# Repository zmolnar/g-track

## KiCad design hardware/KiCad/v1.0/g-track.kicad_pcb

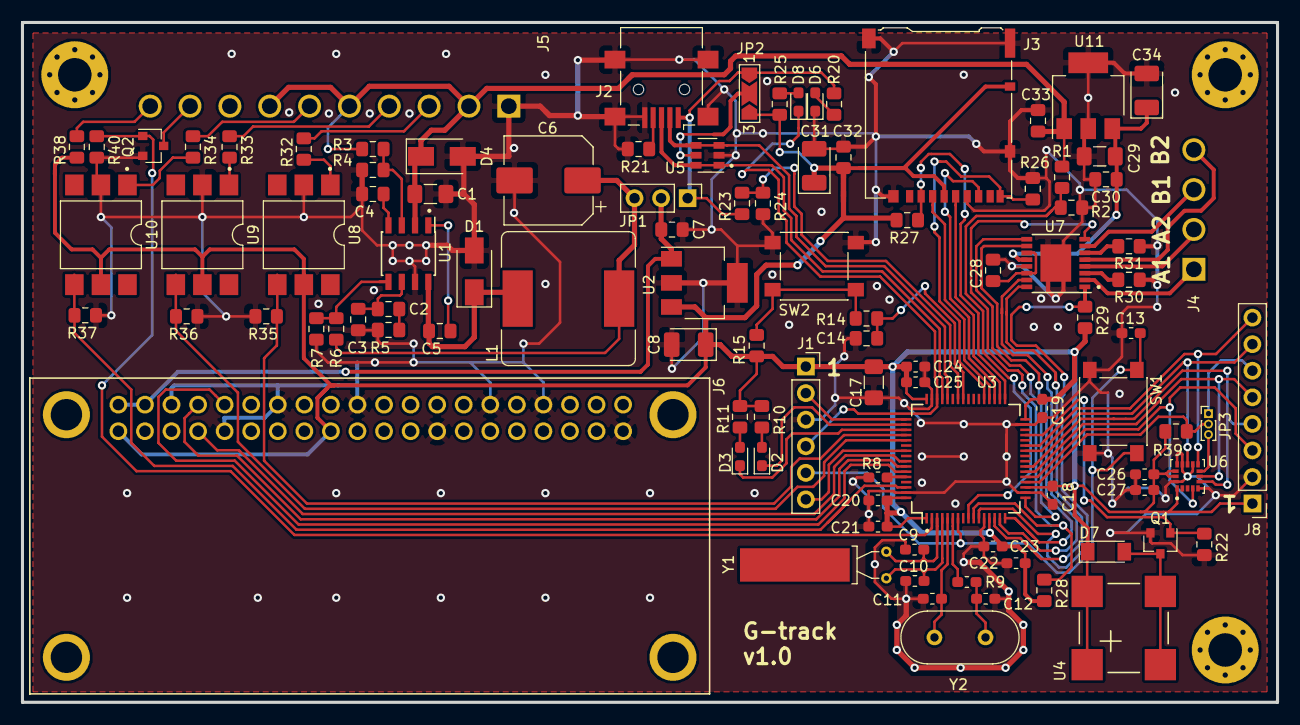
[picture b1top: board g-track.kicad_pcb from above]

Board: 2 copper layers, 120.0 x 65.0 mm, 101 parts (0 on the bottom side), 81 nets.

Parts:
C1, C17, C29: 10uF/25V; C_1206_3216Metric_Pad1.42x1.75mm_HandSolder
C2: 220pF; C_0805_2012Metric_Pad1.15x1.40mm_HandSolder
C3: 56pF; C_0805_2012Metric_Pad1.15x1.40mm_HandSolder
C4: 15nF; C_0805_2012Metric_Pad1.15x1.40mm_HandSolder
C5, C14, C32: 100nF; C_0805_2012Metric_Pad1.15x1.40mm_HandSolder
C6: 470uF; CP_Elec_8x10
C7, C33: 470nF; C_0805_2012Metric_Pad1.15x1.40mm_HandSolder
C8, C31, C34: 47uF; CP_EIA-3528-21_Kemet-B_Pad1.50x2.35mm_HandSolder
C9, C10: 12pF; C_0603_1608Metric_Pad1.05x0.95mm_HandSolder
C11, C12: 22pF; C_0603_1608Metric_Pad1.05x0.95mm_HandSolder
C13, C18, C19, C20, C21, C23, C25, C27: 100nF; C_0603_1608Metric_Pad1.05x0.95mm_HandSolder
C22, C24: 1uF; C_0603_1608Metric_Pad1.05x0.95mm_HandSolder
C26: 10uF; C_0603_1608Metric_Pad1.05x0.95mm_HandSolder
C28: 2.2uF; C_0805_2012Metric_Pad1.15x1.40mm_HandSolder
C30: 100nF/50V; C_0805_2012Metric_Pad1.15x1.40mm_HandSolder
D1, D4: B340A; D_SMA
D2, D3, D6: GREEN; D_0603_1608Metric_Pad1.05x0.95mm_HandSolder
D7: LL46; D_MiniMELF
D8: RED; D_0603_1608Metric_Pad1.05x0.95mm_HandSolder
J1: SWD; PinSocket_1x06_P2.54mm_Vertical
J2: USB_B_Mini; USB_Mini-B_Lumberg_2486_01_Horizontal
J3: Micro SD card; microSD_HC_Hirose_DM3AT-SF-PEJM5
J4: DCM; Tianli_TLPHC100R_1x04_P3.81mm_Horizontal
J5: EXT; Tianli_TLPHC100R_1x10_P3.81mm_Horizontal
J6: Waveshare GSM/GPS/GNSS; Waveshare_GSM_GPS_GNSS_hat
J8: LIS3DSH; PinHeader_1x08_P2.54mm_Vertical
JP1: Power source; PinHeader_1x03_P2.54mm_Vertical
JP2: Protection; SolderJumper-3_P2.0mm_Open_TrianglePad1.0x1.5mm_NumberLabels
JP3: ACC_SPI_SELECT; PinHeader_1x03_P1.00mm_Vertical
L1: 22uH; L_Bourns_SRR1260
Q1, Q2: 2N7002; SOT-23
R1: 75k; R_0805_2012Metric_Pad1.15x1.40mm_HandSolder
R2, R35, R36, R37: 15k; R_0805_2012Metric_Pad1.15x1.40mm_HandSolder
R3: 332k; R_0805_2012Metric_Pad1.15x1.40mm_HandSolder
R4: 68k1; R_0805_2012Metric_Pad1.15x1.40mm_HandSolder
R5: 40k2; R_0805_2012Metric_Pad1.15x1.40mm_HandSolder
R6, R15, R22, R26, R27, R28, R29, R39, R40: 10k; R_0805_2012Metric_Pad1.15x1.40mm_HandSolder
R7: 1k91; R_0805_2012Metric_Pad1.15x1.40mm_HandSolder
R8: 10k; R_0603_1608Metric_Pad1.05x0.95mm_HandSolder
R9: 390R; R_0603_1608Metric_Pad1.05x0.95mm_HandSolder
R10, R11, R25, R38: 330R; R_0805_2012Metric_Pad1.15x1.40mm_HandSolder
R14: 160R; R_0805_2012Metric_Pad1.15x1.40mm_HandSolder
R20: 510R; R_0805_2012Metric_Pad1.15x1.40mm_HandSolder
R21: 100k; R_0805_2012Metric_Pad1.15x1.40mm_HandSolder
R23: 33k; R_0805_2012Metric_Pad1.15x1.40mm_HandSolder
R24: 68k; R_0805_2012Metric_Pad1.15x1.40mm_HandSolder
R30, R31: 0R47; R_0805_2012Metric_Pad1.15x1.40mm_HandSolder
R32, R33, R34: 2k; R_0805_2012Metric_Pad1.15x1.40mm_HandSolder
SW1: Reset; SW_SPST_PTS645
SW2: BT0; SW_SPST_PTS645
U1: TPS54233; SOIC-8_3.9x4.9mm_P1.27mm
U2: LM3940IMP*; SOT-223-3_TabPin2
U3: STM32L452RCTx; LQFP-64_10x10mm_P0.5mm
U4: KSSGJ4B20
U5: USBLC6-2SC6; SOT-23-6
U6: LIS3DSH; LGA-16_3x3mm_P0.5mm_LayoutBorder3x5y
U7: DRV8848; TSSOP-16-1EP_4.4x5mm_P0.65mm
U8, U9, U10: CNY17-3; SMDIP-6_W9.53mm
U11: LM2940IMP*; SOT-223-3_TabPin2
Y1: 32.768kHz; Crystal_AT310_D3.0mm_L10.0mm_Horizontal_1EP_style1
Y2: 8MHz; Crystal_HC49-U_Vertical

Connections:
+3V3: C8.1, C17.1, C18.1, C19.1, C20.1, C21.1, C22.1, C23.1, C24.1, C25.1, C26.1, C27.1, C31.1, C32.1, D7.1, J1.1, J3.4, J3.10, J6.1, J6.17, J8.1, JP2.3, R10.1, R11.1, R15.1, R25.1, R27.1, R28.1, R29.1, R38.1, R39.1, U2.3, U3.1, U3.13, U3.19, U3.32, U3.48, U3.64, U4.1, U4.2, U6.1, U6.14, U6.15, U8.5, U9.5, U10.5
+5V: C7.2, J6.2, J6.4, JP1.2, U2.1
+5V_USB: J2.1, JP1.1, JP2.1, R20.1, R23.1
+12V: C29.1, C30.1, C34.1, U7.12, U11.3
+BATT: C1.1, C33.1, D4.1, J5.2, J5.5, J5.7, R1.1, R3.1, U1.2, U11.1
-BATT: C1.2, C3.2, C4.2, C6.2, C7.1, C8.2, C9.1, C10.1, C11.2, C12.2, C13.2, C14.2, C17.2, C18.2, C19.2, C20.2, C21.2, C22.2, C23.2, C24.2, C25.2, C26.2, C27.2, C28.1, C29.2, C30.2, C31.2, C32.2, C33.2, C34.2, D1.2, D4.2, D6.1, J1.3, J2.5, J2.6, J3.6, J3.11, J5.1, J6.6, J6.9, J6.14, J6.20, J6.25, J6.30, J6.34, J6.39, J8.2, Q1.2, Q2.2, R2.2, R4.2, R5.2, R7.2, R8.2, R21.2, R22.2, R24.2, R26.2, R30.1, R31.1, R35.2, R36.2, R37.2, R40.2, SW1.1, SW2.2, U1.7, U2.2, U3.12, U3.18, U3.31, U3.47, U3.63, U5.2, U6.5, U6.10, U6.12, U6.13, U6.16, U7.13, U7.17, U8.2, U9.2, U10.2, U11.2
/DC motor driver/DCM_AIN1: U3.14, U7.16
/DC motor driver/DCM_AIN2: U3.15, U7.15
/DC motor driver/DCM_BIN1: U3.17, U7.9
/DC motor driver/DCM_BIN2: U3.16, U7.10
/DC motor driver/DCM_FAULT: R28.2, U3.10, U7.8
/DC motor driver/DCM_SLEEP: R29.2, U3.11, U7.1
/External/EXT_IGNITION: R35.1, U3.52, U8.4
/External/EXT_LED: Q2.1, R40.1, U3.2
/External/EXT_SW1: R37.1, U3.62, U10.4
/External/EXT_SW2: R36.1, U3.53, U9.4
/External/IGNITION: J5.3, R32.1
/External/LED_ANODE: J5.10, R38.2
/External/LED_CATHODE: J5.9, Q2.3
/External/SW-1: J5.6, R34.1
/External/SW-2: J5.4, R33.1
/Peripherals/ACC_CS: JP3.2, R39.2, U3.20
/Peripherals/ACC_INT1: J8.7, U3.26, U6.11
/Peripherals/ACC_INT2: J8.8, U3.27, U6.9
/Peripherals/ACC_MISO: J8.5, U3.22, U6.7
/Peripherals/ACC_MOSI: J8.4, U3.23, U6.6
/Peripherals/ACC_SCK: J8.3, U3.21, U6.4
/Peripherals/BUZZER_PWM: Q1.1, R22.1, U3.29
/Peripherals/RPI_UART_RX: J6.10, U3.59
/Peripherals/RPI_UART_TX: J6.8, U3.58
/Peripherals/SDC_CARD_DETECT: J3.9, R26.1, U3.37
/Peripherals/SDC_CS: J3.2, R27.2, U3.33
/Peripherals/SDC_MISO: J3.7, U3.35
/Peripherals/SDC_MOSI: J3.3, U3.36
/Peripherals/SDC_SCK: J3.5, U3.34
/Peripherals/USB_D+: J2.3, U3.45, U5.1, U5.6
/Peripherals/USB_D-: J2.2, U3.44, U5.3, U5.4
/Peripherals/USB_LED: D8.1, J1.4, U3.46
/Peripherals/USB_VBUS_SENSE: R23.2, R24.1, U3.42
/Peripherals/WAVESHARE_POWER: J6.7, U3.57
/Sheet5C1D43B5/ADC_VBAT: R1.2, R2.1, U3.9
/mcu/BOOT0: R8.1, U3.60
/mcu/NRST: C13.1, J1.5, SW1.2, U3.7
/mcu/PA8: C14.1, R14.2, U3.41
/mcu/PA14: J1.2, U3.49
/mcu/PA15: D2.1, U3.50
/mcu/PB3: J1.6, U3.55
/mcu/PC10: D3.1, U3.51
/mcu/PC14: C9.2, U3.3, Y1.1
/mcu/PC15: C10.2, U3.4, Y1.2
unnamed: C2.1, C3.1, U1.6
unnamed: C2.2, R5.1
unnamed: C4.1, U1.4
unnamed: C5.1, U1.1
unnamed: C5.2, D1.1, L1.1, U1.8
unnamed: C6.1, JP1.3, L1.2, R6.1
unnamed: C11.1, U3.5, Y2.1
unnamed: C12.1, R9.2, Y2.2
unnamed: C28.2, U7.11, U7.14
unnamed: D2.2, R10.2
unnamed: D3.2, R11.2
unnamed: D6.2, R20.2
unnamed: D7.2, Q1.3, U4.3, U4.4
unnamed: D8.2, R25.2
unnamed: J2.4, R21.1
unnamed: J4.1, U7.2
unnamed: J4.2, U7.4
unnamed: J4.3, U7.7
unnamed: J4.4, U7.5
unnamed: J8.6, JP3.1
unnamed: JP2.2, U5.5
unnamed: JP3.3, U6.8
unnamed: R3.2, R4.1, U1.3
unnamed: R6.2, R7.1, U1.5
unnamed: R9.1, U3.6
unnamed: R14.1, R15.2, SW2.1
unnamed: R30.2, U7.3
unnamed: R31.2, U7.6
unnamed: R32.2, U8.1
unnamed: R33.2, U9.1
unnamed: R34.2, U10.1

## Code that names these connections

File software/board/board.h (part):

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/*
 * GPIOA setup:
 *
 * PA0  - DCM_AIN1                  (output push-pull).
 * PA1  - DCM_AIN2                  (output push-pull).
 * PA2  - DCM_BIN2                  (input pullup).
 * PA3  - DCM_BIN1                  (input pullup).
 * PA4  - ACC_CS                    (input pullup).
 * PA5  - ACC_SCK                   (input pullup).
 * PA6  - ACC_MISO                  (input pullup).
 * PA7  - ACC_MOSI                  (input pullup).
 * PA8  - BT0                       (input pullup).
 * PA9  - USB_VBUS_SENSE            (input pulldown).
 * PA10 - PA10_NC                   (input pullup).
 * PA11 - USB_DM                    (input pullup).
 * PA12 - USB_DP                    (input pullup).
 * PA13 - SWDIO_USB_LED             (alternate 0).
 * PA14 - SWCLK                     (alternate 0).
 * PA15 - LED_2_RED                 (output push-pull).
 */
#define VAL_GPIOA_MODER             (PIN_MODE_OUTPUT(GPIOA_DCM_AIN1)          | \
                                     PIN_MODE_OUTPUT(GPIOA_DCM_AIN2)          | \
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/*
 * GPIOB setup:
 *
 * PB0  - ACC_INT1                  (input pullup).
 * PB1  - ACC_INT2                  (input pullup).
 * PB2  - PB2_NC                    (input pullup).
 * PB3  - SWD_SWO                   (input pullup).
 * PB4  - PB4_NC                    (input pullup).
 * PB5  - WAVESHARE_POWER           (output push-pull).
 * PB6  - RPI_UART_TX               (input pullup).
 * PB7  - RPI_UART_RX               (input pullup).
 * PB8  - PB8_NC                    (input pullup).
 * PB9  - EXT_SW1                   (input push-pull pull-down).
 * PB10 - BUZZER_PWM                (output push-pull).
 * PB11 - PB11_NC                   (input pullup).
 * PB12 - SDC_SPI2_CS               (alternate 5).
 * PB13 - SDC_SPI2_SCK              (alternate 5).
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 * GPIOC setup:
 *
 * PC0  - PC0_NC                    (input pullup).
 * PC1  - ADC_VBAT                  (input pullup).
 * PC2  - DCM_FAULT                 (input pullup).
 * PC3  - DCM_SLEEP                 (output pullup).
 * PC4  - PC4_NC                    (input pullup).
 * PC5  - PC5_NC                    (input pullup).
 * PC6  - SDC_CARD_DETECT           (input pulldown).
 * PC7  - PC7_NC                    (input pullup).
 * PC8  - PC8_NC                    (input pullup).
 * PC9  - PC9_NC                    (input pullup).
 * PC10 - LED_3_GREEN               (output push-pull).
 * PC11 - EXT_IGNITION              (input push-pull pull-down).
 * PC12 - EXT_SW2                   (input push-pull pull-down).
 * PC13 - EXT_LED                   (output push-pull).
 * PC14 - OSC32_IN                  (input pullup).
 * PC15 - OSC32_OUT                 (input pullup).
 */
#define VAL_GPIOC_MODER             (PIN_MODE_INPUT(GPIOC_PC0_NC)             | \
                                     PIN_MODE_INPUT(GPIOC_ADC_VBAT)           | \
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
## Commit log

2018-07-18 Add readme file.
2018-07-18 Add ChibiOS as a submodule.
2018-09-22 Remove submodule.
2019-02-12 Add ChibiOS 18.2.x 5b8695ccbd8388b7ac880d57fb1fdbc9a0d4c6ca to the project. Add STM32L432 demo project as a base.
2019-02-28 Add v1.0 hardware design docs.
2019-03-05 Add support for STM32L452RC MCU. Not tested.
2019-03-05 Correct gitignore file.
2019-03-20 Add USB serial port driver and shell thread.
2019-03-25 Add SD-card over SPI support.
2019-03-26 Refactor threads and code structure.
2019-03-28 Add first implementation of SIM8xx modem driver.
2019-04-01 Manage control signal to reset the waveshare modem.
2019-04-10 Fix GPIO setup for SDC data pins.
2019-05-12 Reorganize code and add support for GPS module
2019-05-12 Move hardware design files to v1.0 directory.
2019-05-15 Add AT command library.
2019-05-15 Update blueprint template files
2019-05-15 Add CGNSPWR and CGNSINF to the AT library
2019-05-15 Add corrections to fix compilation errors.
2019-05-15 Implement logging of position data on SD card
2019-05-16 Do some code formatting
2019-05-16 Add todo file
2019-05-16 Add dashboard to the project.
    Define the basic structure and interface of the dashboard module and
    implement position data handling.
2019-05-16 Fix compilation issues.
2019-05-16 Add .vscode to gitignore list
2019-05-17 Modify STM32L4 registry to configure RTC.
2019-05-20 Add system info file handling to peripheral manager thread.
2019-05-20 Modify the interface of dashboard to make object independent.
2019-05-20 Add chain oiler thread to the project.
2019-05-20 Fix bug.
2019-05-20 Implement DC motor driver functionality.
2019-05-20 Fix system info file name.
2019-05-20 Add RTC to the system.
    Add RTC to the dashboard and update clock when needed, based on the GPS data.
2019-05-21 Add day-of-week calculation
    Implement Zeller's congruence algorithm.
2019-05-22 Add release notes file to track major releases.
2019-05-22 Fix typo
2019-05-22 Modify PeripheralManagerThread to use mailbox instead of events.
    Remove Board events from the project and remove all references from
    BoardMonitorThread too.
2019-05-22 Fix compilation errors.
2019-05-23 Refactor DC motor driving logic
2019-05-23 Modify GPS reader thread to use mailbox instead of semaphore.
2019-05-23 Simplify code
    Clean up thread interfaces, remove events, use mailboxes instead of.
2019-05-23 Enable kernel debug checks and correct bug.
2019-05-24 Add logfile for chain oiler thread
2019-05-24 backup commit, rewrite this
2019-05-25 Add forced mode to chain oiler and some minor improvements.
2019-05-28 Configure Fatfs to use RTC.
2019-05-29 Add time management to the dashboard
    Implement unified and convenient time handlers and update related parts of the
    threads.
2019-05-29 Correct pull-down config of some GPIO and extend system state machine handler.
2019-05-31 Implement state macine in GPS reader thread.
2019-05-31 Add state machine and error strings to System thread.
2019-05-31 Reorganize stats machine handling in the threads. Still not tested.
2019-05-31 Fix minor issues.
2019-06-05 Fix chain oiler timing calculation.
2019-06-05 Clean up the code a little.
2019-06-06 Add external switch handling to board monitor thread.
2019-06-06 Modify BT0 handling.
    When the button is pressed shorter than 1 sec, then unmount the SD card,
    otherwise force the chain oiler to work.
2019-06-06 Add mutex to protect SD card against unexpected removal.
2019-06-06 Add reverse direction for the DC motort driver.
2019-06-06 Add one-shot command to Chainoiler thread.
    When EXTSW1 is pressed, a single oil drop is released.
2019-06-06 Do some code clean up.
2019-06-06 Add checks before doing mount/unmount.
2019-06-06 Fix OS lock related error.
2019-06-07 Modify EXT SW1 function.
    Release one oil drop for a short press.
    Start chain oiler force mode when pressed longer then 1 sec.
2019-06-07 Turn external LED ON when DC motor is driver.
2019-06-12 Add clang-format config file.
2019-06-12 Apply clang-format on the source files.
2019-06-12 Fine tune oil drop release method.
2019-10-09 Refactor board monitor thread.
2019-10-10 Refactor ChainOilerThread.
2019-10-10 Fix compilation issues. Not tested yet.
2019-10-23 Modify chain oiler scheduling. Not tested yet.
2019-10-26 Modify heartbeat thread to display GPS state and fix bugs in chain oiler.
2019-10-28 Fine-tune chain oiler method.
2019-10-29 Refactor GpsReaderThread.
2019-10-30 Refactor Dashboard.
2019-10-30 Refactor SystemThread.
2019-10-30 Add minor fixes.
2019-10-31 Refactor SD card handler.
2019-10-31 Refactor board monitor.
2019-10-31 Refactor debug shell.
2019-10-31 Refactor peripheral manager.
2019-10-31 Refactor shell commands.
2019-10-31 Refactor ATlib and SIM8XX driver.
2019-11-01 Remove chibios tests from the app.
2019-11-10 First working prototype. Heavy refactor is needed.
2019-11-16 Refactor SIM driver. Still not ready.
2019-11-17 Improve bluetooth connection handling.
2019-11-20 Partial, backup commit.
2019-11-20 Backup commit.
2019-11-21 Partial commit
2019-11-22 Partial commit.
2019-11-22 Remove URC processor thread.
2019-11-22 Replace char with uint8_t and remove unnecessary buffer copies.
2019-11-22 Add fixes.
2019-11-23 Backup commit. Do not use.
2019-11-24 Add parser to the SIM handler. Add ceedling tests as well.
2019-11-24 Fix sim8xx reader thread.
2019-11-24 Add failing test case for the parser to solve.
2019-11-25 Add some new tests for parser.
2019-11-25 Improve parser.
2019-11-25 Move ceedling build root to build/ceedling.
2019-11-25 Add state diagrams to the documentation.
2019-12-20 Remove old sim8xx related files and add sim8xx repo as a submodule.
2020-01-05 Add SimHandlerThread and start the integration. Work on progress.
2020-01-06 Update sim8xx submodule.
2020-01-06 It can be compiled, but cleanup is needed. Work in progress.
2020-01-06 Implement Bluetooth related functionality. Extend the SimHandler implementation.
2020-01-06 Fix minor issues and do first smoke tests.
2020-01-07 Fix main.c formatting.
2020-01-07 Minor fixes.
2020-01-07 Make Bluetooth work with the new sim8xx parser. More work needed.
2020-01-07 Update sim8xx parser submodule.
2020-01-08 Minor corrections.
2020-01-12 Increase modem startup time to 3 sec and update sim8xx.
2020-01-13 Update sim8xx.
2020-01-15 Use HSE and LSE instead of MSI as main clock source.
2020-01-18 Configure SWO pin.
2020-01-18 Add SWO trace for SIM868 communication.
2020-01-25 Add config definition and config manager thread.
2020-01-25 Addply minIni stash from previous state.
2020-01-26 Add config for bluetooth connection. More sync is needed. Fix bluetooth event handling.
2020-02-17 Add MotionDetectorThread and accelerometer handling.
2020-02-18 Add issue list.
2020-02-18 Refactor MotionDetectorThread a little.
2020-02-28 Add blueprint templates for creating AT commands and tests.
2020-03-02 Fix bug in ChibiOS configuration. The sytick timer was changed to a 16 bit timer, but the configuration was not adapted.
2020-03-02 Add ReporterThread to the system.
2020-03-02 Update ReporterThread and some related functionalities.
2020-03-02 Remove BoardMonitorThread and let the external events handled by PeripheralManager.
    Add event for system update.
2020-03-02 Add event for signaling succesfull config load.
2020-03-02 Add corrections.
2020-03-03 Restructure PeripheralManagerThread.
2020-03-03 Modify PeripheralManager and SIM868 handling.
2020-03-03 Fix Modem startup sequence.
2020-03-05 Add configuration for GPRS and SIM. Modify corresponding threads as well. Fix bug related to SD card locking in ConfigManagerThread.
2020-03-05 Fix BT0 and SW1 handler, it was a mistake. Software debouncing is needed, it is to be implemented later.
2020-03-06 Update peripheral manager to read config before setting up the modem. Update event handling too.
2020-03-06 Add config for GPS, Motiondetector and fix minor issues.
2020-03-06 Update config of MotionDetector and Gps.
2020-03-06 Fix event handling issues in PeripheralManager.
2020-03-06 Initialize shell from BluetoothManagerThread init function.
2020-03-09 Fix missing initialization of pointer.
2020-03-09 Add Record_t to handle records and adapt ReporterThread too.
2020-03-09 Add config for the vehicle and fine-tune ReporterThread.
2020-03-10 Improve record buffer handling.
2020-03-10 Implement RecordBuffer_t and adapt ReporterThread too. Add ceedling test folder.
2020-03-10 Continue report sending when sending of previous report is done.
2020-03-10 Fix bug in RecordBuffer handling.
2020-03-11 Blink external LED when GPRS communication is ongoing.
2020-03-12 Improve ReporterThread to resend data when transmission failed and postpone stop command when transaction is pending.
2020-03-12 Reconnect when device gets disconnected from GPRS.
2020-03-12 Increase RecordBuffer to store 2 minutes of data.
2020-03-12 Switch ON external LED while GPRS communication is ongoing.
2020-03-15 Fix bugs in ReporterThread message handling.
2020-03-16 Remove error state from GpsReaderThread. Remove status shell command.
2020-03-16 Remove error state from SystemThread.
2020-03-16 Modify record serializer to use MySql datetime string format for the date.
2020-03-16 Modify record serialization to fit v3 database layout.
2020-03-21 Add AT logging to SimHandler.
2020-03-21 Make IP connection more robust and add signal strength and system state to the reported record.
2020-03-22 Handle HTTP error 600 and above and add logging to ReporterThread.
2020-03-22 Add chain oiler control for switch 1.
2020-03-23 Fix one-shot command handling in ChainOilerThread and PeripheralManagerThread.
2020-03-23 Increase SIM logger fifo depth and add small test.
2020-03-24 Switch back to 32 bit systick timer.
2020-03-24 Fine tune chain oiler release timing.
2020-03-24 Fix error handling, if HTTP GET failed to send.
2020-03-26 Fix bug in ReporterThread when reconnecting to the GPRS network.
2020-04-06 Stop HTTP and GPRS service before attempting to reconnect to mobile network.
2020-04-08 Fine tune event handling when GPRS transaction failed.
2020-04-15 Refactor ReporterThread. Not ready yet.
2020-05-01 Minor fix.
